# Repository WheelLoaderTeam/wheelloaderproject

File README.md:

wheelloaderproject
==================

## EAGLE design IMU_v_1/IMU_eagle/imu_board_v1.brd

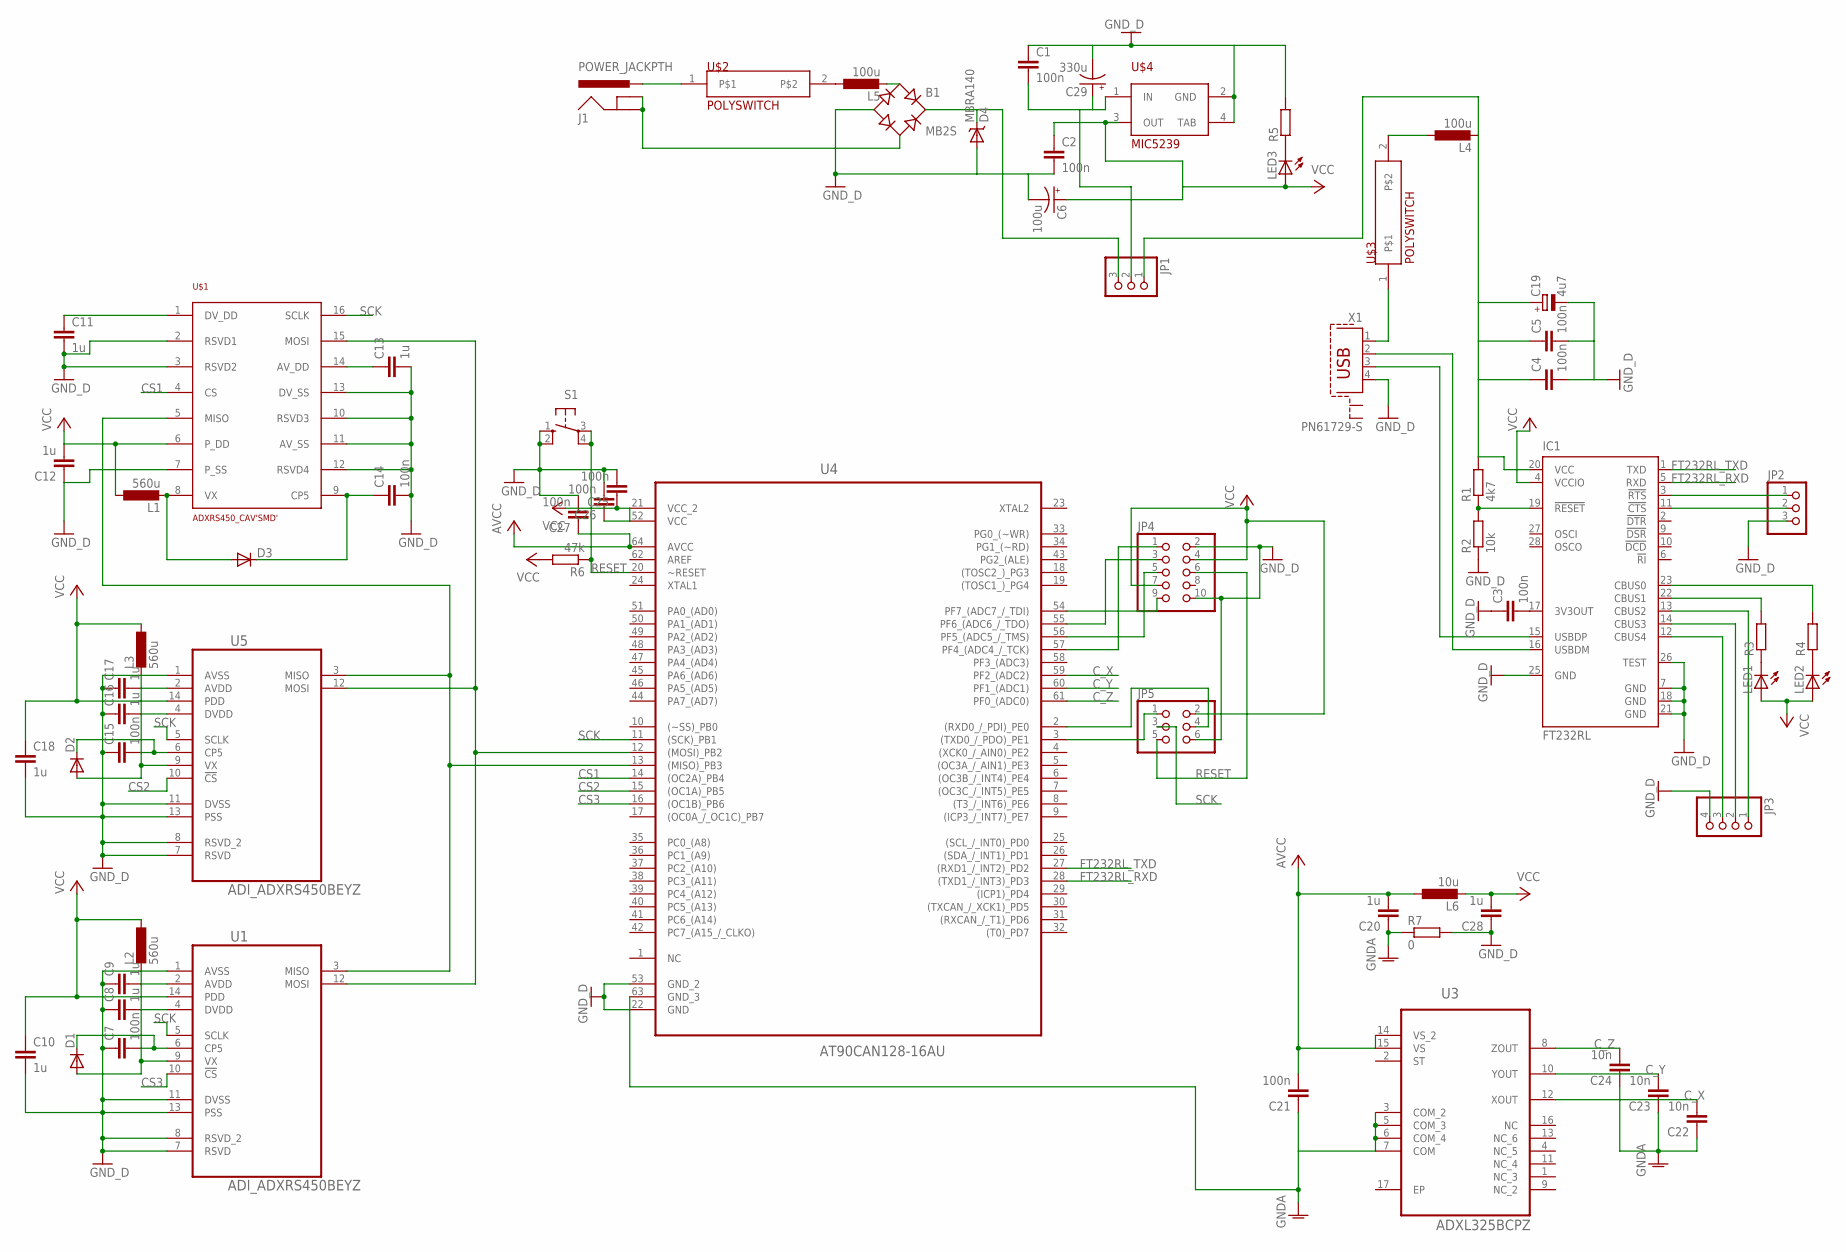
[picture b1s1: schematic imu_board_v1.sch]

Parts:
B1: MB2S; SOIC-4
C1, C2, C3: 100n; 0603-CAP
C4, C5, C7, C14, C15, C21, C25, C26, C27: 100n; C0603
C6: 100u; PANASONIC_G
C8, C9, C10, C11, C12, C13, C16, C17, C18, C20, C28: 1u; C0603
C19: 4u7; 153CLV-0405
C22, C23, C24: 10n; C0603
C29: 330u; PANASONIC_G
D1, D2, D3: DIODE-SOD123; SOD123
D4: MBRA140; SMA-DIODE
IC1: FT232RL; SSOP28
J1: POWER_JACKPTH; POWER_JACK_PTH
JP1, JP2: PINHD-1X3; 1X03
JP3: PINHD-1X4; 1X04
JP4: PINHD-2X5; 2X05
JP5: PINHD-2X3; 2X03
L1, L2, L3: 560u; L1812
L4, L5: 100u; L1812
L6: 10u; L1812
LED1, LED2, LED3: LEDCHIPLED_0603; CHIPLED_0603
R1: 4k7; R0603
R2: 10k; R0603
R3, R4, R5: R-EU_R0603; R0603
R6: 47k; R0603
R7: 0; M1206
S1: 10-XX; B3F-10XX
U1, U5: ADI_ADXRS450BEYZ; ADI_ADXRS45XXXX
U3: ADXL325BCPZ; QFN65P400X400X150-17N
U4: AT90CAN128-16AU; QFP80P1600X1600X120-64N
U$1: ADXRS450_CAV'SMD'; SOIC_CAV_16
U$2, U$3: POLYSWITCH; FUSE
U$4: MIC5239; SOT-223-3
X1: PN61729-S

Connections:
AVCC: C20.2, C21.2, C27.1, L6.1, U3.14 (VS_2), U3.15 (VS), U4.64 (AVCC)
CS1: U4.14 ((OC2A)_PB4), U$1.4 (CS)
CS2: U4.15 ((OC1A)_PB5), U5.10 (!CS)
CS3: U1.10 (!CS), U4.16 ((OC1B)_PB6)
C_X: C22.2, U3.12 (XOUT), U4.59 (PF2_(ADC2))
C_Y: C23.2, U3.10 (YOUT), U4.60 (PF1_(ADC1))
C_Z: C24.2, U3.8 (ZOUT), U4.61 (PF0_(ADC0))
FT232RL_RXD: IC1.5 (RXD), U4.28 ((TXD1_/_INT3)_PD3)
FT232RL_TXD: IC1.1 (TXD), U4.27 ((RXD1_/_INT2)_PD2)
GND: B1.-, C1.1, C2.2, C3.1, C4.2, C5.2, C6.-, C7.1, C8.1, C9.1, C10.2, C11.2, C12.1, C13.2, C14.2, C15.1, C16.1, C17.1, C18.2, C19.-, C25.2, C26.2, C27.2, C28.1, C29.-, D4.A, IC1.7 (GND), IC1.18 (GND), IC1.21 (GND), IC1.25 (GND), IC1.26 (TEST), JP2.3, JP3.4, JP4.2, JP4.10, JP5.6, R2.1, R5.2, R7.2, S1.1 (S), S1.2 (S1), U1.1 (AVSS), U1.7 (RSVD), U1.8 (RSVD_2), U1.11 (DVSS), U1.13 (PSS), U4.22 (GND), U4.53 (GND_2), U5.1 (AVSS), U5.7 (RSVD), U5.8 (RSVD_2), U5.11 (DVSS), U5.13 (PSS), U$1.2 (RSVD1), U$1.3 (RSVD2), U$1.7 (P_SS), U$1.10 (RSVD3), U$1.11 (AV_SS), U$1.12 (RSVD4), U$1.13 (DV_SS), U$4.2 (GND), U$4.4 (TAB), X1.4
GNDA: C20.1, C21.1, C22.1, C23.1, C24.1, R7.1, U3.3 (COM_2), U3.5 (COM_3), U3.6 (COM_4), U3.7 (COM), U4.63 (GND_3)
unnamed: J1.PWR, U$2.1
unnamed: L5.1, U$2.2
unnamed: B1.~2 (AC2), J1.GND, J1.GNDBREAK
unnamed: C1.2, C29.+, JP1.2, U$4.1 (IN)
unnamed: D3.A, L1.2, U$1.8 (VX)
unnamed: JP4.1, U4.57 (PF4_(ADC4_/_TCK))
unnamed: JP4.3, U4.55 (PF6_(ADC6_/_TDO))
unnamed: U$3.1, X1.1
unnamed: IC1.16 (USBDM), X1.2
unnamed: C9.2, U1.2 (AVDD)
unnamed: C8.2, U1.4 (DVDD)
unnamed: C7.2, D1.C, U1.6 (CP5)
unnamed: C13.1, U$1.14 (AV_DD)
unnamed: IC1.15 (USBDP), X1.3
unnamed: C14.1, D3.C, U$1.9 (CP5)
unnamed: C11.1, U$1.1 (DV_DD)
unnamed: C3.2, IC1.17 (3V3OUT)
unnamed: IC1.19 (!RESET), R1.1, R2.2
unnamed: D1.A, L2.2, U1.9 (VX)
unnamed: B1.+, D4.C, JP1.3
unnamed: LED1.C, R3.1
unnamed: LED2.C, R4.1
unnamed: C17.2, U5.2 (AVDD)
unnamed: C16.2, U5.4 (DVDD)
unnamed: C15.2, D2.C, U5.6 (CP5)
unnamed: D2.A, L3.2, U5.9 (VX)
unnamed: IC1.22 (CBUS1), R3.2
unnamed: IC1.23 (CBUS0), R4.2
unnamed: L4.1, U$3.2
unnamed: IC1.3 (!RTS), JP2.1
unnamed: IC1.11 (!CTS), JP2.2
unnamed: IC1.13 (CBUS2), JP3.1
unnamed: JP5.1, U4.3 ((TXD0_/_PDO)_PE1)
unnamed: IC1.14 (CBUS3), JP3.2
unnamed: IC1.12 (CBUS4), JP3.3
unnamed: LED3.C, R5.1
unnamed: B1.~1 (AC1), L5.2
unnamed: JP5.4, U4.2 ((RXD0_/_PDI)_PE0)
unnamed: JP4.5, U4.56 (PF5_(ADC5_/_TMS))
unnamed: C4.1, C5.1, C19.+, IC1.20 (VCC), JP1.1, L4.2, R1.2
unnamed: U1.12 (MOSI), U4.12 ((MOSI)_PB2), U5.12 (MOSI), U$1.15 (MOSI)
unnamed: JP4.9, U4.54 (PF7_(ADC7_/_TDI))
unnamed: U1.3 (MISO), U4.13 ((MISO)_PB3), U5.3 (MISO), U$1.5 (MISO)
RESET: JP4.6, JP5.5, R6.1, S1.3, S1.4 (P1), U4.20 (~RESET)
SCK: JP5.3, U1.5 (SCLK), U4.11 ((SCK)_PB1), U5.5 (SCLK), U$1.16 (SCLK)
VCC: C2.1, C6.+, C10.1, C12.2, C18.1, C25.1, C26.1, C28.2, IC1.4 (VCCIO), JP4.4, JP4.7, JP5.2, L1.1, L2.1, L3.1, L6.2, LED1.A, LED2.A, LED3.A, R6.2, U1.14 (PDD), U4.21 (VCC_2), U4.52 (VCC), U5.14 (PDD), U$1.6 (P_DD), U$4.3 (OUT)

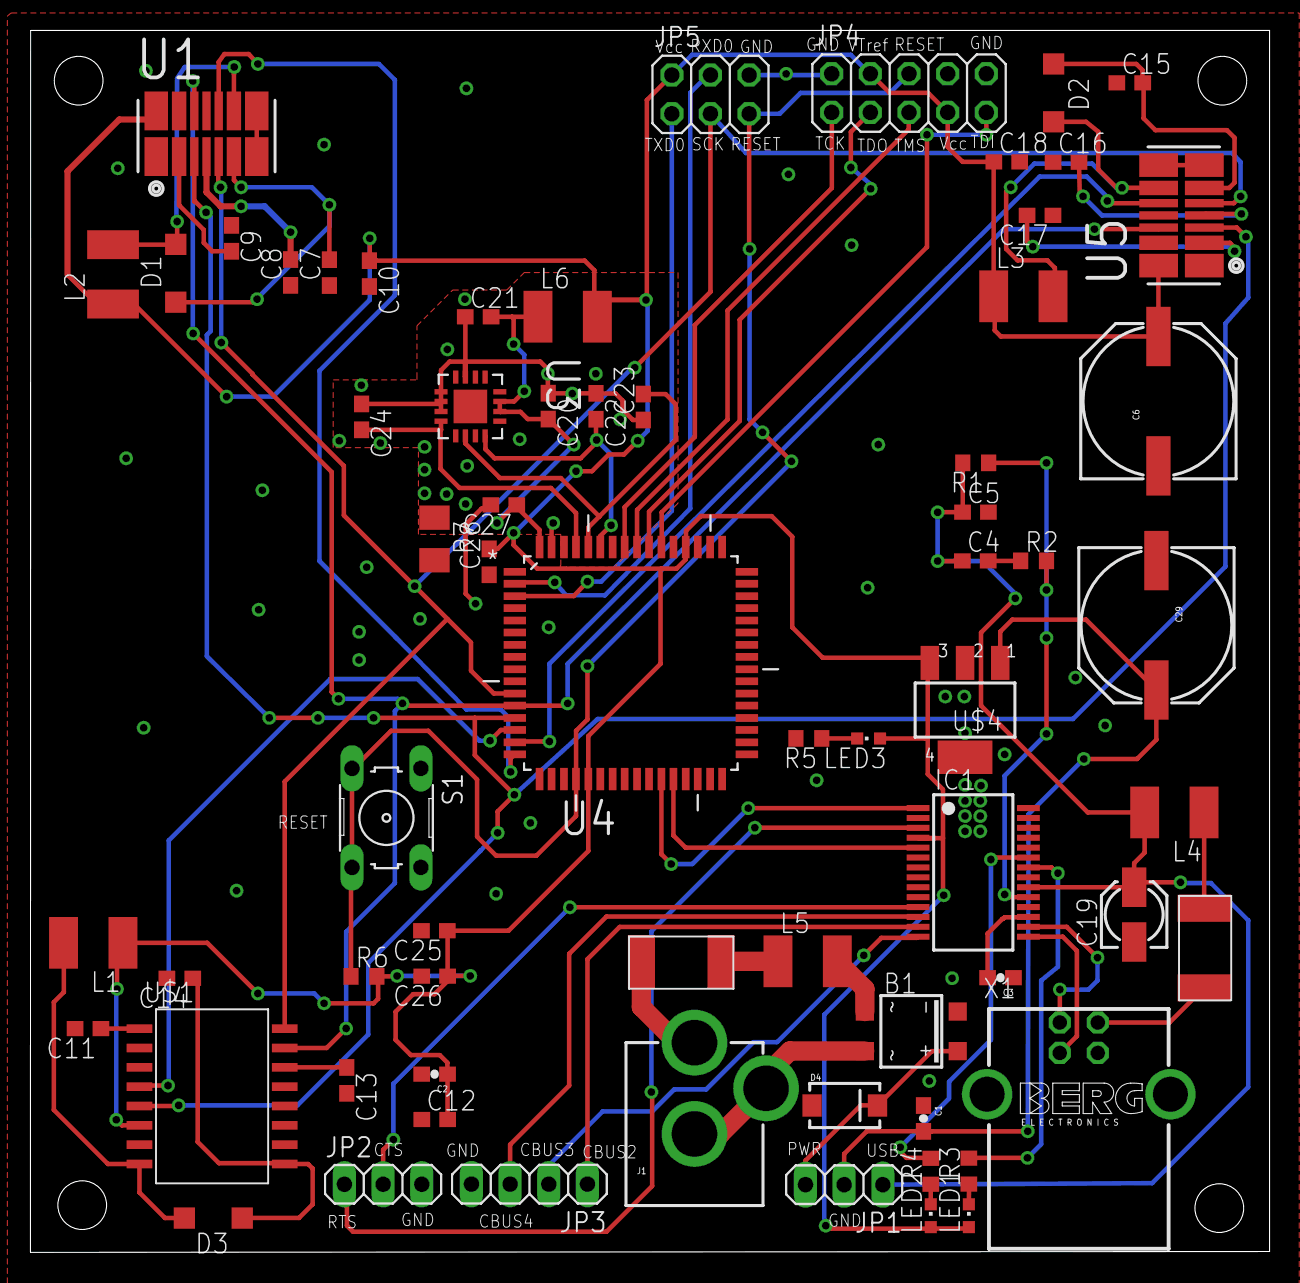
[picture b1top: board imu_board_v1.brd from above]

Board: 2 copper layers, 81.4 x 80.3 mm, 67 parts (0 on the bottom side), 57 nets.

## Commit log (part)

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2013-11-06 Adding HI file
2013-11-06 HI file modified
2013-11-06 Jesper HI file it's me
2013-11-06 Daniel Not burning anything down, worry not my friend!!
2013-11-06 JB create IMU_PC_COM project to receive data from the IMU
2013-11-06 Jesper modified HI
2013-11-06 JB mofifi HI
2013-11-06 Max modified HI
2013-11-06 Jesper commiting
2013-11-06 Daniel Committing
2013-11-06 Daniel Modified file client and client.c to allow for local UDP communication.
2013-11-06 Max changes on the main.c file. buffer is noz reset after message is sent
2013-11-06 Jesper, testing
2013-11-06 Jesper, more testing
2013-11-06 Update Jesper_test
2013-11-06 -hihihi
2013-11-06 -bleh
2013-11-06 nudå
2013-11-06 hejhej
2013-11-07 Daniel Committing client and client.c with changes made to IP address for ethernet UDP communication.
2013-11-07 Jesper adding IMU progam files
2013-11-07 test
2013-11-07 Max I add the project for the OryxPc programs and the Socket.h file describing all variables needed for socket communication and general fonctions to handle them
2013-11-07 Moved relayPacket
2013-11-07 relayPacket updated
2013-11-07 adding eagle files
2013-11-07 J. adding updated version of IMU code
2013-11-07 Max implementation of init and die fonction in socket.c file write the first step of IMUHandling.c file the program handling the IMU packet problem in the init fonction release not fonctional modifie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
2013-11-07 Max commiting all
2013-11-08 Jesper
2013-11-11 Moved EBU test scripts to reposatory
2013-11-11 Daniel Adding the "Logging" folder, which contains logger.c, a file created for the purposes of logging data.
2013-11-11 Daniel Adding Code for the Logging portion of the software
2013-11-11 Added analogOutPacket, updated relayPacket
2013-11-11 Daniel Updated the file Logger.c, This change now implements a early working version of the Logger we will be using.
2013-11-11 Jesper, IMU stuff
2013-11-11 Jesper, adding notes for tomorrow
2013-11-13 Daniel Updated the logger. Changes include a filenaming system that labels the log file with the current date and time. Also, algorithm implemented to open a new log file, once the current log file h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
2013-11-13 Max add freauency parameter to the SensorPacketHandling.c file modify the socket.h With adding LEN_BUF_... constants modify in socket.c initSocket fonction to fit uses in the SensorPacketHandling pro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
2013-11-13 Max add timer to handle frequency add parameter to change frequency add constants for buffer lenght in socket.h modify initSocketfunc in the socket.c file to fit its purpose in the rest of the program
2013-11-13 Updated ebu packets
2013-11-13 Max find a bug while testing we need to set the tv values at every loop so now it's done
2013-11-13 Jesper, end of the day
2013-11-14 Jesper, removing junk
2013-11-14 updated ebu packets test
2013-11-14 Jesper, end of day
2013-11-15 added analogInPacket
2013-11-15 Daniel Adding the Logger.h file, which includes the function header declerations.
2013-11-15 changed permissions
2013-11-15 Daniel Changed Logger.c function names to start with lowercase first letter, followed by capital letters.
2013-11-15 Max add sending fonctions
2013-11-15 minor change
2013-11-15 Revert "changed permissions"
    This reverts commit f407dddfe74a36880df7bf6f134b91f2945aa818.
    undo changed permissions
2013-11-15 Daniel Adding SNTP code found from http://ftp.cc.uoc.gr/mirrors/OpenBSD/src/usr.sbin/rdate/ntp.c This code will be used for synchronizing PC's to the NTP clock, and also for timestamping logged data.
2013-11-15 Updaded and cleaned up in EBU_packets
2013-11-15 Jesper, fixed timing (hopefully)
2013-11-18 cleanup of socket
2013-11-18 fixed socket.c. aton() depricated. using pton() instead
2013-11-18 Daniel Adding more example code for NTP synchronization. Filename ntpdate.c
2013-11-18 fixed socket.h and socket.c
2013-11-18 updated EBUtest to have socket functions
2013-11-18 Jesper, things are weird on my computer
2013-11-18 Daniel Adding a new file for recording TimeStamps. Filename Timestamp.c
2013-11-18 Daniel Minor changes to Timestamp.c.
2013-11-18 fixed another problem with socket.c causing binding errors /n updated EBUtest
2013-11-19 updated socket.c and EBUtest
2013-11-19 Upadted EBUtest and fixed some problems in the packet types
2013-11-19 Daniel Adding code that will be used for handling the Acceleration and Gyro Data. Specifically, the code implements an algorithm for calibrating the gyros and accelerometer whenever the loader is at 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
2013-11-20 Updaded EBUtest
2013-11-20 Max modify SensorPacketHandling so it can handle early packet handling TODO modify a bit more to discard "very early" packet only mode 1 is implemented
2013-11-20 Begun work on the command part of onboard pc programs
2013-11-20 Daniel committing changes to parse.c
2013-11-21 removed obselete test code in EBU_packets
2013-11-21 updated onBoardControl
2013-11-21 Daniel Added in multiple features for dealing with the raw IMU data.
2013-11-22 Daniel Major changes made to support rcv and send buffers. Beginnning to code rcv and send functions.
2013-11-22 Max created sensor data struct to handle the packet received and send them created a fake client and server to test our code (general so everyone can use it) ready for testing
2013-11-22 Daniel Created functions loadGyroSendBuffer(...) and init(). Have not yet been tested and proven to work properly.
2013-11-22 Daniel. Added a comment to the code.
2013-11-22 Max begin testing. added a lot of printf :p
2013-11-24 updated onBoardComand
2013-11-25 Daniel Major changes to parse.c. Will not be using buffers to send and receive the data, as timing is not critical at this stage of the system. Rather the code will send the data as soon as it is rec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
2013-11-26 Daniel Changed function names, added main.c code for handling gyro packet data.
2013-11-27 Daniel - Testing the git functionality on my personal machine. //Testing Git on Personal Machine - Comment should show up in commit
2013-11-27 Daniel - Now using structs to handle packet loads. Code Reflects this
2013-11-28 renamed controlPackets to commandPackets
2013-11-29 Max Write a new simpler loop to Handle DataSensor packets loop description inside the folder
2013-11-29 Updated socket.h with correct port numbers for the EBU
2013-11-29 Compiles properly, need to write sendData() function before testing.
2013-11-29 Daniel Implemented the traversing of the saveBuffer, yet need to implement the writing of the savebuffer
2013-12-02 Updated onBoard control and begun testing
2013-12-02 All aglorithms in place. sendData() needs to be written, along with recvData(), and a startup algorithm is needed.
2013-12-02 Added to int main a startup algorithm, which loads the buffer and checks for stationary state. This continues until the tractor is known to be in a stationary state, at which point the program moves 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
2013-12-02 Daniel- Need to modify to a single function call, with no main function.
2013-12-02 Jesper, expanding IMU code
2013-12-02 Jesper, started expanding receive code
2013-12-03 + Added channel defines in EBUanalogIn and EBUanalogOut + Updated OnBoardControl
2013-12-03 Restructered parse.c, renamed to processdata.c, also created a header file processdata.h. Thanks to Andrey for the help.
2013-12-03 Jesper, IMU code that works! (without intterupt routine, TODO)
2013-12-03 Jesper, receive from IMU code that works (with some configs)
2013-12-04 renamed onBoardContol to onBoardCommand
2013-12-04 Jesper, adding receivesensorData
2013-12-04 Max I forget to set the new value of the timer now it's working the sento() fonctions aren't working when I'm not in a long TIMEOUT situation there are a lot of useless printf for debugging
2013-12-04 Added OnSiteCommand
2013-12-04 Added in Network code to for sending packets to OryxPC - Daniel
2013-12-04 Daniel
2013-12-04 Jesper, fixed coordinates. Added a tweaking playground
2013-12-04 Daniel Created receiveSensorData.h
2013-12-04 Max the code is working problem with time is corrected I put a wrong argument in the recvfrom() fonction. It changes the port of the sending socket somehow and now it's working there is still aa prob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
2013-12-04 Jesper, UNDER CONSTRUCTION: adding error handling
2013-12-04 added test with keyboard
2013-12-05 Jesper, removed error messades, need to decide what to return when error data is observed
2013-12-05 modified test code
2013-12-05 Daniel - Changed filename from main.c to receiveSensorData.c
2013-12-05 Daniel - Modified processdata.c and receiveSensorData.h to proceed with integration.
2013-12-05 Updated onSiteCommand
2013-12-05 processdata.c and processdata.h ready for integration
2013-12-05 Updated OnBoardCommand
2013-12-05 Daniel - Rename to Main.c
2013-12-05 Other updates
2013-12-05 Renamed processdata.c and deleted
2013-12-05 Jesper, removing unused files
2013-12-05 Jesper, cleaning up, moving things to Process_Send...
2013-12-05 Jesper, putting all together2
2013-12-05 Daniel deleting obsolete files
2013-12-05 Upated OnBoardCommand after tests @ Karlsvik
2013-12-05 Jesper, code working ugly fix
2013-12-05 Jesper, playing with my tweaking file
2013-12-06 Daniel - Fixed a bug where ss_flag was never being set to false, line 110
2013-12-06 Daniel Minor changes to main.c and header file. Implemented a check against asin NAN errors.
2013-12-06 Changed onBoardCommand to printout some statisic
2013-12-06 modified CommandTestClient
2013-12-06 Max put the real value for port and IP for sockets still bug with time
2013-12-06 Daniel - Trying to debug processData
2013-12-06 Daniel - Debugging ProcessData
2013-12-06 Max just put some note on the sensordatahandling 2 and disabled sending
2013-12-06 Daniel Debugging ProcessData
2013-12-06 Jesper, nothing
2013-12-06 Debugging
2013-12-06 Jesper, debugging (also some OryxPC things I haven't touched
2013-12-06 Jesper, debugging
2013-12-09 Max Modify the name of SensorData.h in SensorDataHandling.h and modify the files calling it Implementation of smoothMovement fonction taking care of rough movement preventing destroying the simulator
2013-12-09 added EBUmonitor and updated onboardCommand
2013-12-09 Daniel - fixed main.c, calibration of X and Y were switched around
2013-12-09 Max implement and use of smooth movement implementation not finished of the nice exit
2013-12-09 Daniel - A Satisfactory solution for gyro data has been implemented and is worrking.
2013-12-10 Prepared onBoardCommand for test
2013-12-10 Jesper, added a print to file in Process..
2013-12-10 Max finish the interupt fonction when exit program
2013-12-10 Max program is initializing well now we find a correct value fo MAX_ROT_MOV
2013-12-10 Moved timespec functions to new file
2013-12-10 Max add timestamp sending to process IMU data file and handling the new packet and calcul delay stats in the SensorPacketHandling file
2013-12-10 Jesper, removing old files
2013-12-10 Added time statistics to "command" communication chain
2013-12-10 Max committing little bugs
2013-12-10 Max committing changes with timestamp on the ProcessIMU file and changes on the client as well
2013-12-11 Jesper, tweaking IMU2
2013-12-11 Mqx last changes in my code
2013-12-12 Jesper, finished logging coes
2013-12-12 Jesper, fixed timeout problem in OryxSim_PC
2013-12-12 Jesper, adding log data
2013-12-12 Jesper, IMU folder junk
2013-12-16 Max commit comment on code and READ ME files creation
2013-12-18 Daniel - Deleting unused directory LoggingCode
2013-12-18 Removed spaces from dir EBU test scripts
2013-12-20 Jesper, adding correct FT232 datasheet
2014-01-08 Jesper, commiting from LAB-PC
2014-01-13 Jesper, rm crap
2014-01-13 Jesper,
2014-01-13 Jesper, programmed new IMU
2014-01-13 Jesper, programmed last IMU.
2014-01-13 Jesper, cleaning up
2014-01-15 Jesper, reverting changes made for code to Johans IMU
2014-01-15 Jesper, cleaning up branch on SSD comp
2014-01-15 Jesper, compiling changes
2014-01-24 Jesper, touching up in IMU code
2014-02-28 Delete READ ME
    Duplicated file
2014-02-28 Delete READ ME
    Duplicate..
2014-02-28 Jesper, removing IMU_PC_COM, old unused program?

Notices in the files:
parts and their libraries:
SparkFun-Connectors: Licensing: CC v3.0 Share-Alike You are welcome to use this library for commercial purposes.
